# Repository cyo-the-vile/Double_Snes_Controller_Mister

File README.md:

# Double_Snes_Controller_Mister
PCB to use Two snes controller on MISTER fpga

This is PCB to hold two SNES controller connectors using the Arduino Pro micro firmware by MickGyver. This lets you use wires or wireless SNES controllers for MISTER FPGA.

You will need an Arduino Pro Micro and Two SNES controller connectors.  Straight or Right angle connectors are totally fine. It's a beginner friendly project to assemble. 

There are mounting holes on 3 points on PCB.  I would just use nylon plastic support screws but you could possible 3D print a case for this.

To order PCB please go to gerber folder and download the ZIP file and take it to a recommended PCB manufacturer such as JLCPCB.

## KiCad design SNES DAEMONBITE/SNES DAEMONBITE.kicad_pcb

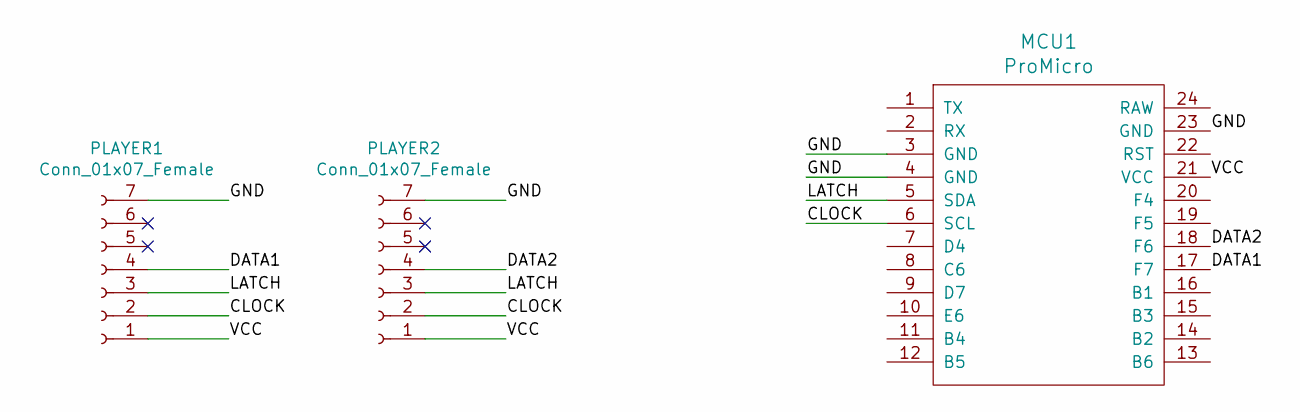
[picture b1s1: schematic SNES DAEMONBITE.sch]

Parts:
MCU1: ProMicro
PLAYER1, PLAYER2: Conn_01x07_Female; snes_connector

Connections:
/CLOCK: MCU1.6 (SCL), PLAYER1.2, PLAYER2.2
/DATA1: MCU1.17 (F7), PLAYER1.4
/DATA2: MCU1.18 (F6), PLAYER2.4
/GND: MCU1.3 (GND), MCU1.4 (GND), MCU1.23 (GND), PLAYER1.7, PLAYER2.7
/LATCH: MCU1.5 (SDA), PLAYER1.3, PLAYER2.3
/VCC: MCU1.21 (VCC), PLAYER1.1, PLAYER2.1

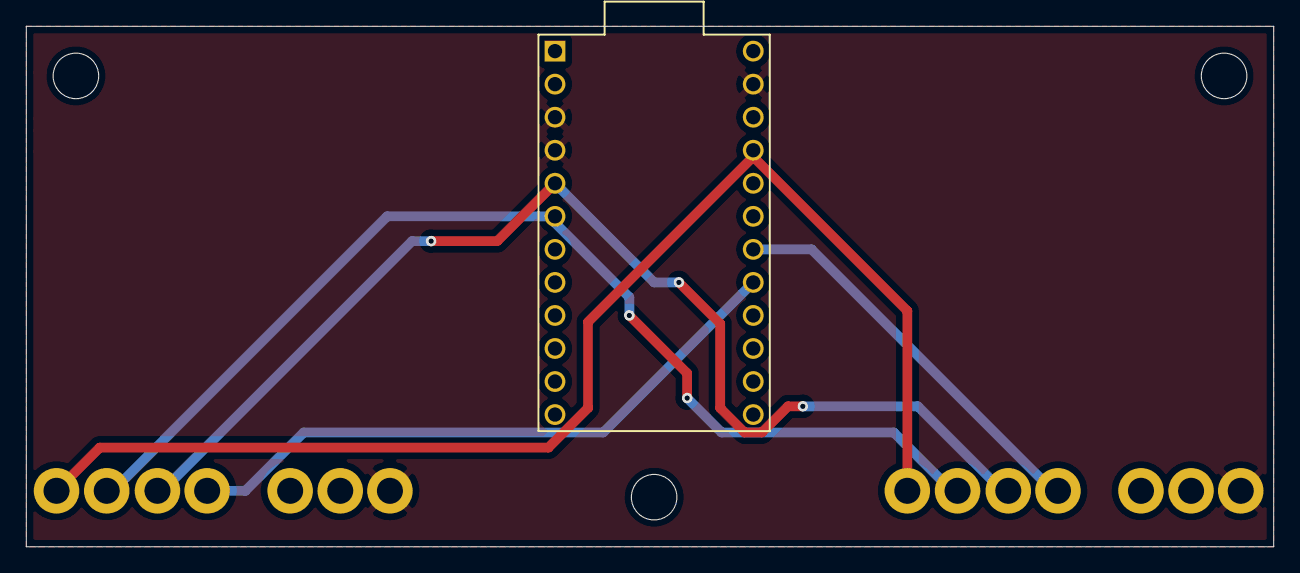
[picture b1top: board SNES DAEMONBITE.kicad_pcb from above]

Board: 2 copper layers, 95.9 x 40.0 mm, 3 parts (0 on the bottom side), 6 nets.

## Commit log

2021-09-24 Update README.md
    Initial commit
2023-06-15 -1P Board added
    -Add Simple 1 Player board. Basically an interposer.
2023-06-15 12341234
    qwr1234`12ef
